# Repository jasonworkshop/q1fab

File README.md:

# q1fab

Q1 fab 0.0.1 still under development, keep an eye out for stable releases.

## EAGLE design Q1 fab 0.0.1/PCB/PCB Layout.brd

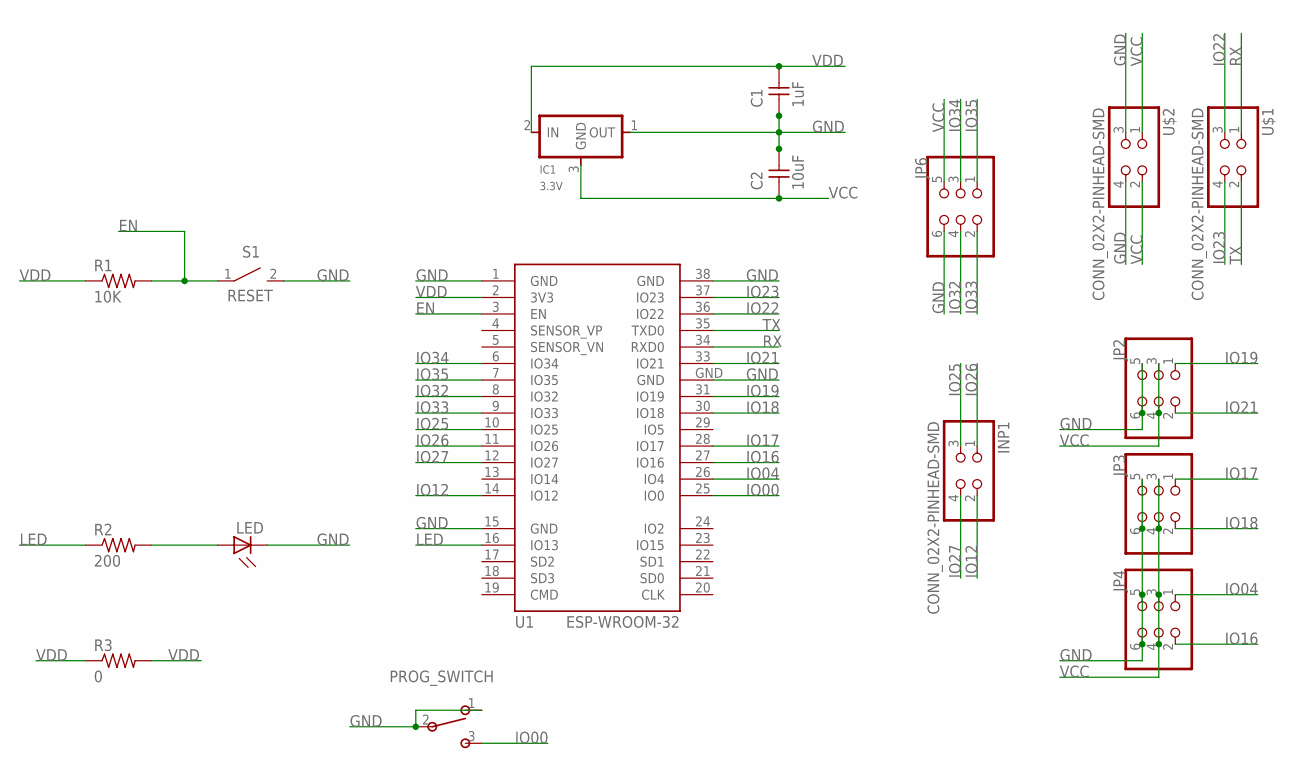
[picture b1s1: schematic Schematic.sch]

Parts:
C1: 1uF; C1206FAB
C2: 10uF; C1206FAB
IC1: 3.3V; SOT23
INP1: CONN_02X2-PINHEAD-SMD; 2X02SMD
JP2, JP3, JP4, JP6: CONN_03X2-PINHEAD-SMD; 2X03SMD
LED: LEDFAB1206; LED1206FAB
PROG_SWITCH: SW_SLIDE-SWITCH; AYZ0102AGRLC
R1: 10K; R1206FAB
R2: 200; R1206FAB
R3: 0; R1206FAB
S1: RESET; B3U-1000P(M)
U1: ESP-WROOM-32
U$1, U$2: CONN_02X2-PINHEAD-SMD; 2X02SMD

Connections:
EN: R1.2, S1.1, U1.3 (EN)
GND: C1.1, C2.2, IC1.1 (OUT), JP2.5, JP2.6, JP3.5, JP3.6, JP4.5, JP4.6, JP6.6, LED.2 (C), PROG_SWITCH.1, PROG_SWITCH.2, S1.2, U1.1 (GND), U1.15 (GND), U1.38 (GND), U1.GND, U$2.3, U$2.4
IO00: PROG_SWITCH.3, U1.25 (IO0)
IO04: JP4.1, U1.26 (IO4)
IO12: INP1.2, U1.14 (IO12)
IO16: JP4.2, U1.27 (IO16)
IO17: JP3.1, U1.28 (IO17)
IO18: JP3.2, U1.30 (IO18)
IO19: JP2.1, U1.31 (IO19)
IO21: JP2.2, U1.33 (IO21)
IO22: U1.36 (IO22), U$1.3
IO23: U1.37 (IO23), U$1.4
IO25: INP1.3, U1.10 (IO25)
IO26: INP1.1, U1.11 (IO26)
IO27: INP1.4, U1.12 (IO27)
IO32: JP6.4, U1.8 (IO32)
IO33: JP6.2, U1.9 (IO33)
IO34: JP6.3, U1.6 (IO34)
IO35: JP6.1, U1.7 (IO35)
LED: R2.1, U1.16 (IO13)
unnamed: LED.1 (A), R2.2
RX: U1.34 (RXD0), U$1.1
TX: U1.35 (TXD0), U$1.2
VCC: C2.1, IC1.3 (GND), JP2.3, JP2.4, JP3.3, JP3.4, JP4.3, JP4.4, JP6.5, U$2.1, U$2.2
VDD: C1.2, IC1.2 (IN), R1.1, R3.1, R3.2, U1.2 (3V3)

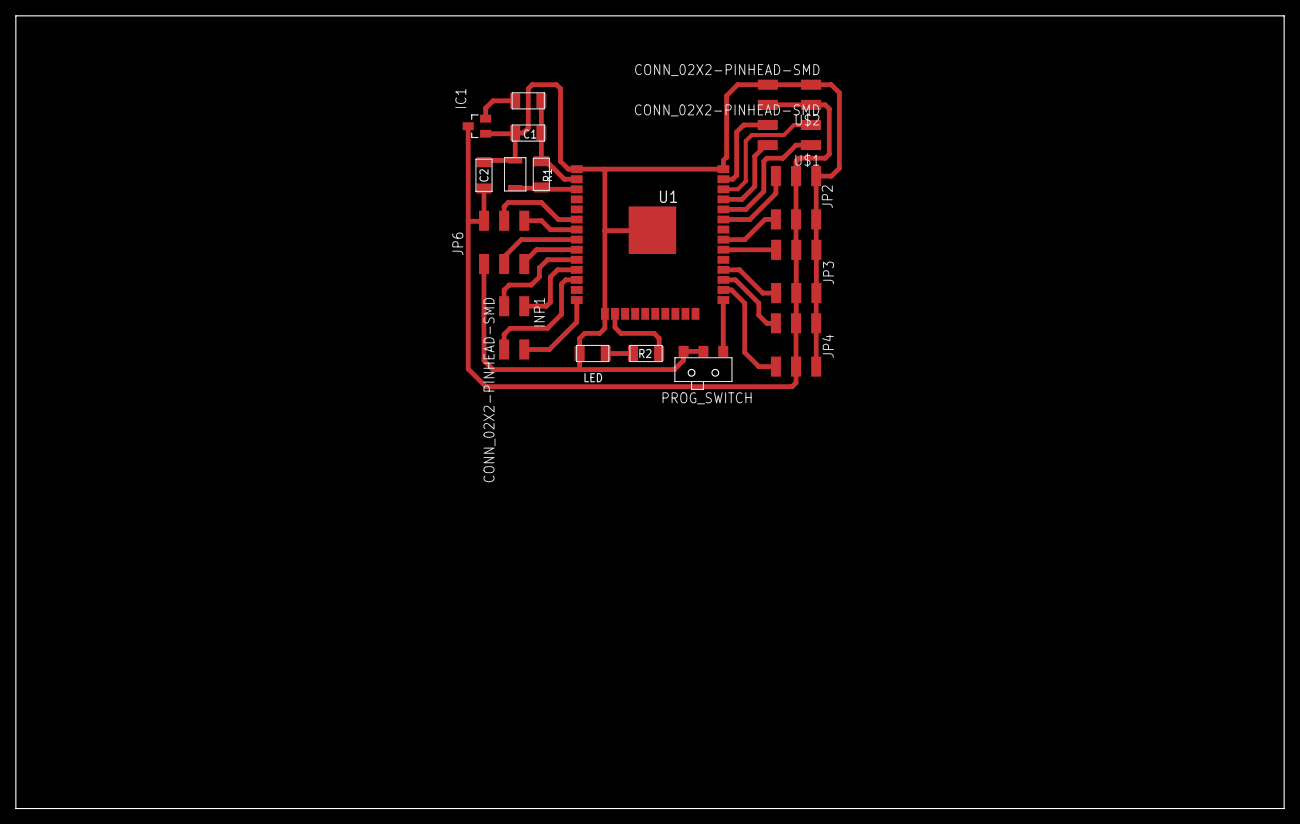
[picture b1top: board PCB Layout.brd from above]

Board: 2 copper layers, 160.0 x 100.0 mm, 17 parts (0 on the bottom side), 25 nets.

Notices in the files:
parts and their libraries:
esp32: Creative Commons Attribution-ShareAlike 4.0 International
